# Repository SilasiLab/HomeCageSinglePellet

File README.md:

# **Overview**:

This system allows the user to host up to 5 mice in their home environment and automatically administer the single pellet reaching test to those animals. The system can run unsupervised and continuously for weeks at a time, allowing all 5 mice to perform an unlimited number of single pellet trials at their leisure. 

The design allows a single mouse at a time to enter the reaching tube. Upon entry, the animal’s RFID tag will be read, and if authenticated, a session will start for that animal. A session is defined as everything that happens from the time an animal enters the reaching tube to when they leave the tube. At the start of a session, the animal’s profile will be read and the task difficulty will be automatically adjusted by moving the pellet presentation arm to the appropriate distance away from the reaching tube. After the difficulty is set, pellets will begin being presented with either the left or right presentation arm, depending on which arm is specified in the mouse’s profile. Pellets will continue to be presented periodically until the mouse leaves the tube, at which point the session will end. Video and other data is recorded for the duration of each session. At session end, all the data for the session is saved in an organized way. 

# **Dependencies:**
* Ubuntu v16.04 LTS: Kernel version 4.4.19-35 or later
* Python v3.5.2
	* pySerial	
	* numpy
	* OpenCV v3.4.x
	* tkinter 
	* matplotlib
	* Pillow
	* tqdm
* Flir Spinnaker SDK v1.10.31
	* libavcodec-ffmpeg56
	* libavformat-ffmpeg56
	* libswscale-ffmpeg3
	* libswresample-ffmpeg1
	* libavutil-ffmpeg54
	* libgtkmm-2.4-dev
	* libusb-1.0-0
	
	Note: The Spinnaker dependencies are installed via official Spinnaker SDK install script.
* Arduino IDE v1.8.5

# **Software Installation:**
1. Install Ubuntu 16.04 LTS on your machine.
2. Install Anaconda. (https://www.anaconda.com/distribution/)
3. Install the Flir Spinnaker SDK v1.10.31 **INSERT GOOGLE DRIVE LINK TO SPINNAKER SDK HERE**
4. Install Arduino IDE v1.8.5. (https://www.arduino.cc/en/Main/Software)
5. Install OpenCV for C++.
	- `sudo apt-get install build-essential cmake git libgtk2.0-dev pkg-config libavcodec-dev libavformat-dev libswscale-dev`
	- `sudo apt-get install libjpeg-dev libpng-dev libtiff5-dev libjasper-dev libdc1394-22-dev libeigen3-dev libtheora-dev 			libvorbis-dev libxvidcore-dev libx264-dev sphinx-common libtbb-dev yasm libfaac-dev libopencore-amrnb-dev 			libopencore-amrwb-dev libopenexr-dev libgstreamer-plugins-base1.0-dev libavutil-dev libavfilter-dev 				libavresample-dev`
	- `sudo -s`
	- `cd /opt`
	- Download OpenCV source from https://github.com/opencv/opencv/releases/tag/3.4.4 and unpack it into /opt
	- Download OpenCV_contrib source from https://github.com/opencv/opencv_contrib/releases/3.4.4 and unpack it into /opt
	- `cd opencv`
	- `mkdir release`
	- `cd release`
	- `cmake -D BUILD_TIFF=ON -D WITH_CUDA=OFF -D ENABLE_AVX=OFF -D WITH_OPENGL=OFF -D WITH_OPENCL=OFF -D WITH_IPP=OFF -D 			WITH_TBB=ON -D BUILD_TBB=ON -D WITH_EIGEN=OFF -D WITH_V4L=OFF -D WITH_VTK=OFF -D BUILD_TESTS=OFF -D 				BUILD_PERF_TESTS=OFF -D CMAKE_BUILD_TYPE=RELEASE -D CMAKE_INSTALL_PREFIX=/usr/local -D 						OPENCV_EXTRA_MODULES_PATH=/opt/opencv_contrib/modules /opt/opencv/`
	- `make j4`
	- `make install`
	- `ldconfig`
	- `exit`
	- `cd`
	- `pkg-config --modversion opencv`
	- If everything worked correctly, output should read "3.4.4".
	
5. Create and configure a virtual environment for installing the HomeCageSinglePellet code.
	- `conda create -n <yourenvname> python=3.5.2 anaconda`
	- `conda activate <yourenvname>`
	- `conda install -c conda-forge opencv=3.4.4`
	- `conda install -c anaconda numpy`
	- `conda install -c anaconda pyserial`
	- `conda install -c anaconda tk`
	- `conda install -c conda-forge matplotlib`
	- `conda install tqdm`
	- `conda install Pillow`

6. Download the HCSP source code from https://github.com/SilasiLab/HomeCageSinglePellet and unpack it.
7. Optional (Only if you want to use the analysis features): Install Deeplabcut using the Anaconda based pip installation method. (https://github.com/AlexEMG/DeepLabCut/blob/master/docs/installation.md)
8. Optional (Only if you want to use the anaylsis features): Move the file `HomeCageSinglePellet/src/analysis/HCSP_analyze.py` into `~/.conda/envs/DLC2/lib/python3.6/site-packages/deeplabcut` (Where DLC2 is the name of the anaconda virtual environment where you installed Deeplabcut).
9. Optional (Only if you want to use the anaylsis features): Download our pretrained DLC2 network for automatically extracting reach attempts from your videos. **INSERT GOOGLE DRIVE LINK TO NETWORK HERE**
8. Done!

# **Assembly:**

### **Prerequisites:**

1. Obtain all the parts listed in `HomeCageSinglePellet/resources/partsList.xls`
2. Have the PCB `HomeCageSinglePellet/resources/PCB/nano.brd` manufactured (Find a manufacturer, send them the .brd file using
whatever process they use for upload, wait for it in the mail).
3. 3D print all the .stl files contained in `HomeCageSinglePellet/resources/CAD/STL/`

### **Attach headers and components to the PCB**

1. Attach female headers for the Arduino onto the PCB. Attach male headers onto the CAMTRIG, MSZ, SERVO1, SERVO2, RFID and
IRBREAK holes on the PCB.

2. Solder the stepper driver to the PCB in the orientation shown in the picture. (Note that the holes on 
the PCB are spaced too far apart for the stepper driver pins). To address this we bend the pins of the driver to fit. You'll 
need to do this until someone gets around to fixing the PCB layout.

3. Solder the capacitor across C1 as shown in the picture. (TODO: INSERT PICTURE)

### **Install the voltage regulator and power connectors**

4. Voltage regulator output must be set to 5V by turning the small screw on the blue pot. This is done my powering the device with 12V and recording the output with multimeter while adjusting the pot screw.
Attach 6 leads to the voltage regulator:
	- 2 Leads to the positive input pad.
	- 2 leads to the negative input pad.
	- 1 lead to the positive output pad.
	- 1 lead to the negative output pad.

5. Short the neutral and ground leads on the circular power connectors by soldering a small wire across them.

6. Line up the voltage regulator in the box and drill holes through the box where you want to mount the regulator.

7. Screw one of the circular power connectors into the bottom hole.

8. Solder one of the negative input leads you attached to the voltage regulator in step 1 onto the negative lead of the 
power connector you screwed in in step 4.

9. Solder one of the positive input leads you attached to the voltage regulator in step 1 onto the positive lead of the
power connector you screwed in in step 4. 

10. Place the PCB into the box and drill holes into the box where the mount holes on the PCB line up. 
Then mount the PCB with some bolts. Metal bolts are fine, they won't touch anything that will be a problem. 
Use nylon washers if you're nervous.

11. Solder the remaining positive input power lead that you attached to the voltage regulator in 
step 5 to the positive MOTORPWR pad on the PCB.

12. Solder the remaining negative input power lead that you attached to the voltage regulator in 
step 5 to the negative MOTORPWR pad on the PCB.

13. Screw in the second circular power connector to the remaining hole in the box. Solder a wire from the negative lead of the
second power connector to the negative lead of the first power connctor. Solder a wire from the positive lead of the second power
connector to the positive lead of the first power connector.

### **Assemble the pellet delivery system and mouse tube**

14. Line the hopper rail piece up on the baseplate and screw in the 4 screws that hold it in place.

15. Attach the stepper motor as shown in the picture. Attach the coupler to the shaft of the motor. **Note:** For the steps involving the stepper motor, coupler and coupling screw; We don't yet have a design that uses standard parts. We currently take the screw detailed in the parts list and cut it and the stepper motor shaft to the correct lenght. **INSERT CORRECT LENGTH OF STEPPER MOTOR SHAFT AND COUPLING SCREW HERE.**

16. Attach the screw to the stepper coupler. Slide the hopper onto the rails and insert the nut into the slot where the stepper coupler screw will go. Then thread the shaft coming out of the coupler into the nut. 

17. Rotate the stepper coupler until the screw is all the way into the hopper nut. Solder two leads to the microswitch,
one each on the left and right prongs coming out of the switch. Use superglue to glue the microswitch down so it will be pressed
when the hopper reaches it's closest point to the motor. 

18. Attach both front surface mirrors to the mirror mount piece with double sided tape.

19. Slide the front-wall/mirror holder piece over the end of the acrylic tube.

20. Use your favorite adhesive to attach the IR-Breaker to the IR-Breaker holder.

21. Slide the IR-Breaker holder over the tube so that the beam runs across the bottom of the tube 
(Where the mice feet will be).

22. Hotglue the RFID reader to the acrylic tube as shown.(Note: Push the IR-Breaker holder up against the RFID module so that 
it's sandwiched between the IR-Breaker holder and the front-wall/mirror holder, and hot glue it all in place).

23. Slot the assembled acrylic tube into the square hole on the rail baseplate mount as shown.

24. Line up both servos as shown in the picture. Rotate the servo splines as far as they will go in the 
directions shown in the picture.

25. Use an allen key to insert the set screws into the tips of the hopper arms.

26. Attach the hopper arms to the servo spline as shown in the picture. (Note: This is why we 
rotated the servo spline as far as possible in step 28, so that you can set the maximum retraction 
point of the hopper arms by attaching them how you like).

27. Line the servos with attached hopper arms up as shown in the picture and use your favourite adhesive to 
adhere them to the servo mount points on the hopper. **Note:** This step can be finicky. Before you adhere the servos to the 
hopper, ensure the hopper arms will rotate easily at their pivot point and that they slide easily through the holes in the 
hopper. If there is too much friction the arms will vibrate and jump around as they move, and since their function is to 
balance millet seeds on a small set screw, vibrations are bad.

28. This step is where we will glue the acrylic tube permanently into the sqaure 3D printed hole it sits in. Rotate the stepper
coupler until the hopper is as close as it can get to the motor. Now rotate the hopper arms up so that they are sitting infront 
of the tube opening as shown. On bootup the stepper motor will "zero" the hopper using the limit switch. We want this zero point
to put our pellet presentation arms directly infront of the tube opening. Additionally we want the tube to sit at a high enough angle that the hopper will not catch on the mirrors or any part of the tube assembly when it moves. Once you're satisfied that both these requirements are met, glue the tube into place. 

29. Splice the power wires of both servo motors together. Splice the ground wires of both servo motors together. Splice the servo power wire into the lead coming out of the voltage regulator positive output. Splice the servo ground wire into the lead coming out of the voltage regulator negative output.

30. Plug the leftmost servo signal wire into the SERV02 signal pin on the PCB. Plug the rightmost servo signal wire into the 
SERVO1 signal pin on the PCB.

31. Splice the power wires of the IRbreak LED and photo diode together. Splice the ground wires of the IRBreak LED and photo diode together. Plug the spliced power, spliced ground and signal line of the IRbreaker into the IRBREAK pins on the PCB. 

32. Plug the microswitch wires into the MSZ pins on the PCB. (TODO: Figure out which wire goes onto which pin and add a picture)

33. Plug the 12V 1A power supply into either of the circulaer power connectors on the PCB box.

34. Plug one of the micro USB cables into the Arduino on one end and the PC on the other.

35. Plug one of the micro USB cables into the Arduino on one end and the PC on the other.

36. Assembly complete!
 
# **Calibration and Configuration:**

1. You'll need to upload the `HomeCageSinglePellet/src/arduino/homecage_server/homecage_server.ino` file to the Arduino. 
(https://www.arduino.cc/en/Guide/ArduinoNano)
NB.:
* A. After a fresh install of Ubuntu, there may be issues accessing serial ports. Run the following command to give full access: sudo usermod -a -G dialout $USER  (in our case user: silasi).
* B. Use following setting in Arduino IDE: 
	- 1. Tools -> Board -> Arduino Nano
	- 2. Tools -> Processor -> Atmega 328P (Old Bootloader)
2. There are 4 constants that will need to be modified in the file
`HomeCageSinglePellet/src/arduino/homecage_server/homecage_server.ino`
They are: `SERVO1_UP_POS`, `SERVO1_DOWN_POS`, `SERVO2_UP_POS` and `SERVO2_DOWN_POS`. They are located
on lines 41,43,45 and 47 respectively. These constants represent the PWM signal going to each servo. I won't explain PWM here,
all you need to know is different numbers correspond to different positions for the servos. In the main loop, lines 421-425 
have a block that will make the arms go up and down one at a time in an infinite loop. You'll need to observe the up/down 
positions of the arms during these movements to dial in the correct position, using the constants mentioned above. I haven't 
found a better way to do this yet, and frankly all the arduino code is poorly written. Any improvements or a rewrite would be 
welcomed. Once you're happy with the up/down position of each arm during their "pellet presenting" movements, comment 
the infinite loop out and upload to the Arduino.
	
2. Open `HomeCageSinglePellet/config/config.txt` and set the path to your `HomeCageSinglePellet/AnimalProfiles/` 
directory. (One of the Spinnaker video writing functions doesn't work with relative paths so we chose to work with 
full paths). I believe python has a library that will turn a relative path into a full path, so this could be fixed in 
the future.
	
3. We don't provide exact details on camera setup, but if you want to use the analysis features provided in this 
project, it will be important to have video recording conditions as close as possible to ours. The performance of 
deelabcut will degrade rapidly as conditions stray from those used to produce the frames used to train the network.
Additionally the functions in kinalyze.py are dependent on specific recording conditions. If you plan to use the analysis 
features, leave the recording settings in `HomeCageSinglePellet/config/config.txt` as the default. In terms of lighting 
conditions, camera mounting, recording angle, etc, just do your best to make it look like the picture below. If it's close 
enough, the analysis pipeline will work. **INSERT PICTURE OF FRAME CAPTURED BY PTGREY**

# **Usage**:
### **Running the Device**
1. Enter the virtual environment that the system was installed in by typing `source activate <my_env>` into a terminal.

2. Use `cd` to navigate to HomeCageSinglePellet/src/client/ and then run `python -B genProfiles.py`. The text prompts will walk you through entering your new animals into the system.

3. Open HomeCageSinglePellet/config/config.txt and set the system configuration you want.

4. Enter HomeCageSinglePellet/src/client/ and run `python -B main.py`

5. To test that everything is running correctly, block the IR beam breaker with something
	and scan one of the system’s test tags. If a session starts properly, it’s working.

6. To shut the system down cleanly; 

	- Ensure no sessions are currently running. 
	- Press the quit button on the GUI.
	- Ctrl+c out of the program running in the terminal.
NB.
1. Arduino needs to be USB0 , and RFID reader needs to be USB1. You can see connected USB devices with terminal command:
ls /dev/tty*

### **Analysis**:

A high level analysis script is provided that runs the data for all animals through a long analysis pipeline. The functions performed on each video include;

* Analyze with Deeplabcut2.
* Identify all reaching attempts and record frame indexes where reaches occur.
* Compute 3D trajectory of reaches and estimate magnitude of movement in millimeters.
* Cut videos to remove any footage not within the bounds of a reaching event.
* Neatly package data for each analyzed video in a descriptively named folder within the animals ./Analyses/ directory.

This analysis is started by entering the HomeCageSinglePellet/src/analysis/ directory and running
`bash analyze_videos.sh <CONFIG_PATH> <VIDEO_DIRECTORY> <NETWORK_NAME>`

This script takes the following input;

**CONFIG_PATH** = Full path to config.yaml file in root directory of DLC2 project.

**VIDEO_DIRECTORY** = Full path to directory containing videos you want to analyze. (e.g <~/HomeCageSinglePellet/AnimalProfiles/MOUSE1/Videos/>)

**NETWORK_NAME** = Full name of DLC2 network you want to use to analyze videos. (e.g <DeepCut_res
net50_HomeCageSinglePelletNov18shuffle1_950000>)

Another script (`HomeCageSinglePellet/src/analysis/scoreTrials.py`) is provided for manually categorizing reaches once they have been identified in the step detailed above. This script opens a GUI that allows the user to select an animal and browse through all the videos that have been analyzed for that animal. (In the video list, blue videos indicate videos where reaches were detected by the analysis software. Beige videos indicate videos where no reaches were detected. Green videos indicate videos that have already been manually scored). When users select a video from the list, the video window will display the first detected reach in a loop. It will also display the "reach count" (e.g 1/16) to indicate how many reaches the video contains and which one is currently being viewed. The user can then use the mouse or a hotkey to place the current reach into a category. The video window will then jump to the next reach. This repeats until all the reaches for a given video are scored, at which point the category information will be saved. 

**Note:** All the analysis functions read and write all their data to/from `HomeCageSinglePellet/AnimalProfiles/<animal_name>/Analyses/`. Information for each video is saved in a unique folder whose name includes video creation date, animal RFID, cage number and session number. (e.g `2019-01-25_14:36:31_002FBE737B99_67465_5233`). Each of these folders will contain the raw video, the deeplabcut output from analyzing the video (.h5 and .csv formats). In addition, if >=1 reaches were found in the video, the folder will contain a file named date_time_rfid_cage_number_session_number_reaches.txt (e.g `2019-01-25_14:36:31_002FBE737B99_67465_5233_reaches.txt`). This file contains the start and stop frame indexes of each reach in the video and (x,y,z) vectors for each reach. In addition, once a video has been scored manually using `scoreTrials.py`, a file named date_time_rfid_cage_number_session_number_reaches_scored.txt (e.g `2019-01-25_14:36:31_002FBE737B99_67465_5233_reaches_scored.txt`) will be added to the video's folder. This file is the same as date_time_rfid_cage_number_session_number_reaches.txt, except that it also contains a category identifier for every reach.

# **Troubleshooting**:

* Is everything plugged in?
* Shutting the system down incorrectly will often cause the camera and camera software to enter a bad state.
	* Check if the light on the camera is solid green. If it is, unplug the camera and plug it back in.
	* Check the HomeCageSinglePellet/src/client/ directory for a file named KILL. If this file exists, delete it.
	* Make sure the camera is plugged into a USB 3.0 or greater port and that it is not sharing a USB bridge with too many 			other devices (I.e if you have 43 devices plugged into the back of the computer and none in the front, plug the 		camera into the front).
* Make sure you are in the correct virtual environment.
* Make sure the HomeCageSinglePellet/config/config.txt file contains the correct configuration. (If the file gets deleted it will be replaced by a default version at system start)
* Make sure there are 1 to 5 profiles in the HomeCageSinglePellet/AnimalProfiles/ directory. Ensure these profiles contain all 		the appropriate files and that the save.txt file for each animal contains the correct information. 
* Make sure that the Arduino mounted as device ttyUSB0 and that the RFID reader mounted as ttyUSB1 in /dev/. If they mounted 
differently, rebooting and attaching them in the correct order will fix the problem.

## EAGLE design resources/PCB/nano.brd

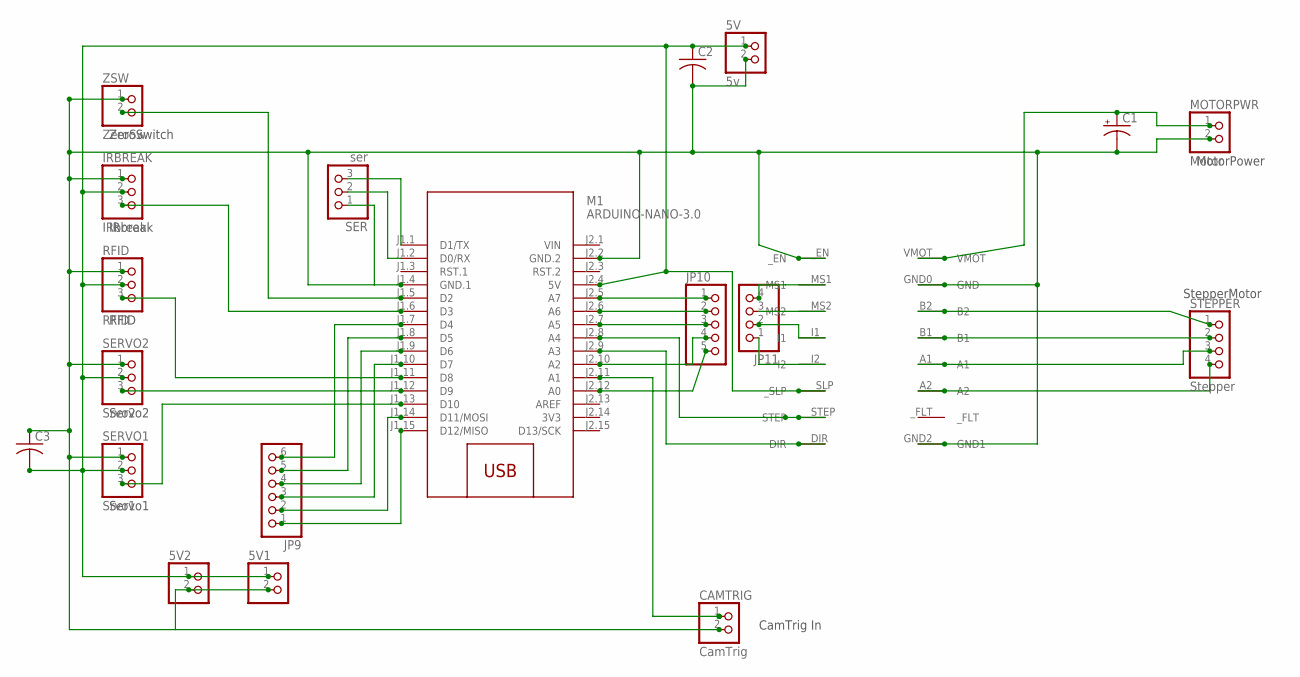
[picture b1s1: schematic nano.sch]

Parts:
5V: 5v; 1X02
5V1, 5V2: PINHD-1X2; 1X02
C1: CPOL-USE5-5; E5-5
C2, C3: C-USC0805; C0805
CAMTRIG: CamTrig; 1X02
IRBREAK: IRbreak; 1X03
JP9: PINHD-1X6; 1X06
JP10: PINHD-1X5; 1X05
JP11: PINHD-1X4; 1X04
M1: ARDUINO-NANO-3.0
MOTORPWR: Motor; 1X02
RFID: RFID; 1X03
SER: ser; 1X03
SERVO1: Srvo1; 1X03
SERVO2: Srvo2; 1X03
STEPPER: Stepper; 1X04
U$1: MP6500
ZSW: ZeroSw; 1X02

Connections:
3V3: M1.J2.14 (3V3)
unnamed: C1.+, MOTORPWR.1, U$1.VMOT
unnamed: JP9.1, M1.J1.15 (D12/MISO)
unnamed: JP11.4, U$1.MS1
unnamed: STEPPER.4, U$1.A2
unnamed: STEPPER.3, U$1.A1
unnamed: STEPPER.2, U$1.B1
unnamed: STEPPER.1, U$1.B2
unnamed: JP9.2, M1.J1.14 (D11/MOSI)
unnamed: JP9.3, M1.J1.10 (D7)
unnamed: M1.J1.12 (D9), SERVO2.3
unnamed: M1.J1.13 (D10), SERVO1.3
unnamed: M1.J1.5 (D2), ZSW.2
unnamed: IRBREAK.3, M1.J1.6 (D3)
unnamed: M1.J1.11 (D8), RFID.3
unnamed: CAMTRIG.1, M1.J2.11 (A1)
unnamed: M1.J2.9 (A3), U$1.DIR
unnamed: M1.J2.8 (A4), U$1.STEP
unnamed: JP9.4, M1.J1.9 (D6)
unnamed: 5V.1, 5V1.1, 5V2.1, C2.1, C3.2, IRBREAK.2, M1.J2.4 (5V), RFID.2, SERVO1.2, SERVO2.2, U$1._SLP
unnamed: JP9.5, M1.J1.8 (D5)
unnamed: JP9.6, M1.J1.7 (D4)
unnamed: JP10.1, M1.J2.5 (A7)
unnamed: JP10.2, M1.J2.6 (A6)
unnamed: JP10.3, M1.J2.7 (A5)
unnamed: JP10.4, M1.J2.10 (A2)
unnamed: JP10.5, M1.J2.12 (A0)
unnamed: 5V.2, 5V1.2, 5V2.2, C1.-, C2.2, C3.1, CAMTRIG.2, IRBREAK.1, M1.J1.4 (GND.1), M1.J2.2 (GND.2), MOTORPWR.2, RFID.1, SER.1, SERVO1.1, SERVO2.1, U$1.GND0 (GND), U$1.GND2 (GND1), U$1._EN, ZSW.1
unnamed: JP11.3, U$1.MS2
unnamed: JP11.2, U$1.I1
unnamed: JP11.1, U$1.I2
unnamed: M1.J1.1 (D1/TX), SER.3
unnamed: M1.J1.2 (D0/RX), SER.2
VIN: M1.J2.1 (VIN)

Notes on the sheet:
Servo1
Servo2
RFID
IRbreak
ZeroSwitch
StepperMotor
MotorPower
CamTrig In

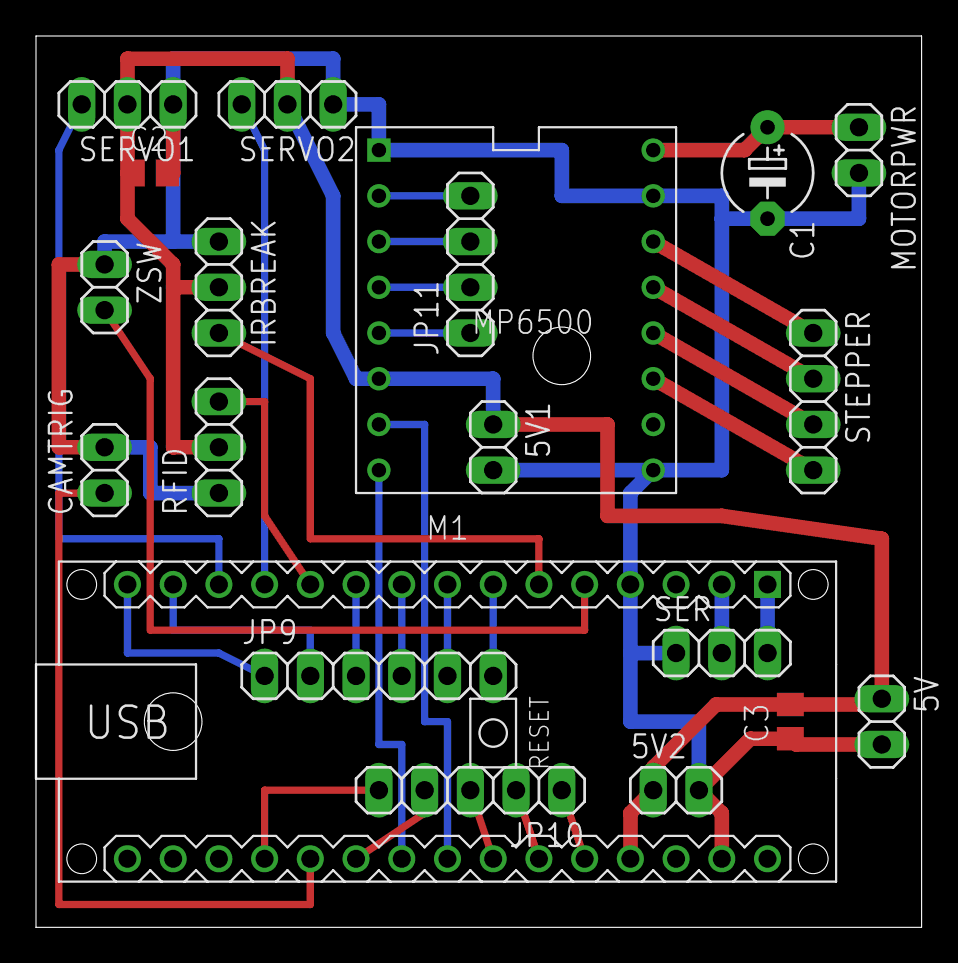
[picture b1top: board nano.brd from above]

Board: 2 copper layers, 49.2 x 49.5 mm, 20 parts (0 on the bottom side), 32 nets.

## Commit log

2018-01-05 Implemented RFID proximity detection and fixed tty buffer issues
2018-01-08 Merged RFID Proximity and IR into GPIO_Control.py and refactored servo control code
2018-01-08 Fixed several typos
2018-01-10 Added camera live feed
2018-01-11 Refactored a bit and started implementing AnimalProfile class
2018-01-11 Started implementing SessionController
2018-01-12 Started putting camera,RFID and servo control into their own classes.
2018-01-12 Version 1 completed. Needs lots of refactoring.
2018-01-13 Refactored
2018-01-13 Renamed SPAutomation.py to main.py
2018-01-15 String formatting, function simplification
2018-01-22 Implemented IR pressence detection, camera recording in separate process and refactored a bit.
2018-01-22 Fixed many typos
2018-01-23 Implemented video recording in forked process and modified existing functions to take advantage of this.
2018-01-23 Made it so PWM signal shuts down after servo moves
2018-01-23 Fixed bugs in camera sub process and implemented PWM kill switch
2018-01-23 Fixed RFID so it is parsed correctly
2018-01-24 Moved servo-arm-cycle to it's own process and improved SessionController.startSession() accordingly
2018-01-24 Fixed bug where RFID tag could be read during an in-progress session, filling the serial buffer.
2018-01-25 Implemented basic logging capability
2018-01-25 Added debug logging to servo process and entered correct RFID profiles for live test
2018-01-30 Worked on commenting things better
2018-02-07 Implemented pellet detection feature
2018-02-07 Debugged and fixed typos
2018-02-07 Put trial_count into session_history logs so we can track trial numbers
2018-03-01 A bunch of minor, random changes...
2018-03-01 Formatted source files to work with Geany
2018-03-01 Added stepper motor control for XY bed feature
2018-03-02 Improved XY bed feature and moved stepper control to long-lived process
2018-03-02 Cleaned things up before weekend overnight test
2018-03-02 Final touchups before weekend overnight test
2018-03-05 Started adding profile save/load feature
2018-03-05 Finished AnimalProfile save/load feature
2018-03-09 Added basic graphing capability of AnimalProfile logs
2018-03-09 Improved comments on some files
2018-03-12 Modified comments
2018-03-12 Finished commenting and moved video path generation to AnimalProfile instead of SessionController.
2018-03-13 Improved console output messages
2018-03-13 Configuring for live use
2018-03-14 Increased stepper motor speed
2018-03-16 Added script to process session_history.csv files into format with human readable date and time for working in excel
2018-04-11 Implementing some of feature backlog from April_10. (untested)
2018-04-12 XY bed now stops immediately when session ends, mouse difficulty level is specified in mm, and log file now has human readable dates instead of timestamps
2018-04-13 Began testing GUI
2018-04-13 Changed AnimalProfile save file format to include more information
2018-04-13 Finished first version of config GUI
2018-06-06 Updating git repo with PC/Arduino/Ptgrey port
2018-06-06 Made it possible to build ptgrey binary from project directory
2018-06-06 Made a dependency list in the INSTALL.txt file
2018-06-11 synced up servo movement signals after Ralph fixed servo wiring
2018-06-20 Updated magic numbers...
2018-07-10 Fixed camera de-initialization failure race condition
2018-07-14 Fixed GUI so animal profile changes made by users will be seen at runtime (untested)
2018-07-16 Removed log file
2018-07-16 Implemented preview window for Spinnaker camera
2018-07-16 Removing camera.py because PS3 camera no longer being used
2018-07-20 Ported plotting function from RPi version to new Arduino/PC version
2018-07-27 Initial commit of DeepLabCut output processing pipeline
2018-07-29 Implemented "Event Extraction" logic for pose event extraction
2018-08-02 Changed Pandas dataframe access from .values to .iat for 100x script speedup
2018-08-13 Implemented analysis scripts for finding successful reaches in video
2018-08-15 Modified config in preparation of running v1.0
2018-08-17 Modified calibration constants....need to put config in environ vars
2018-08-21 Untested fix for AVIOpen hang issue caused by bad string arg
2018-08-24 Set theme jekyll-theme-slate
2018-09-03 Started Successful Reach vs Time graph implementation
2018-09-03 Cleaning up
2018-09-19 Implemented shutdown button in GUI
2018-09-19 Hotfix for GUI
2018-09-19 Made pellet presentation max distance 5 because any higher will derail the hopper
2018-10-22 Added configuration file for spinnaker process.
2018-10-25 Added kinematic analysis to analysis directory
2018-10-25 Did a lot of stuff for fully-automated kinematic 3D-reconsutrction pipeline
2018-10-25 Refactored a tiny bit
2018-10-31 Finished kinalyze dlc point filtering and event parsing
2018-11-04 Finished kinalyze.py
2018-11-21 Swapped out servo library for official Arduino one. Solves servo shooting up problem but introduces servo at-rest jitter
2018-11-21 Removed contents of AnimalProfiles directory....should not have data on github
2018-11-21 Adding AnimalProfiles directory back in....we want the directory here...just needs to be empty
2018-11-21 Changed video file name format, refactored a bit
2018-11-21 TEST tags now bypass config and default to 50FPS and DisplayPreview=True
2018-11-29 Kinalyze is now usable for extracting reaches from videos and generating 3D trajectory reconstructions of those reaches
2018-11-30 Implemented bash wrapper for analyzing directories of videos with DLC and trajectory reconstruction
2018-12-04 Removed deprecated files
2018-12-11 Started implementing semi-auto trial scoring GUI
2018-12-11 Moved RFID functionality to python client
2018-12-12 Made servos detach after every movement (This no longer stalls with Servo.h since removing softwareserial calls). End result is no more jittering!
2019-01-15 ghetto merge
2019-01-15 Updated scoring GUI to prevent videos being cut off as early
2019-01-17 Implemented buttons to select which presenting arm to use for each animal (untested)
2019-01-17 Tested pellet presenting arm control buttons for main gui
2019-01-17 Refactored resources directory structure and added updated ptgrey camera post mount
2019-01-17 Inreased size of through holes on ptgrey camera mount
2019-01-18 Implemented unused video deletion script
2019-01-21 Change kinematic analysis to pad end of events with configurable number of frames
2019-01-21 add pellet classifier
2019-01-22 add the weights of the pellet classification model
2019-01-28 A bunch of changes
2019-01-30 Started documenting system componentsY
2019-01-31 Continuing to comment + document
2019-01-31 Continuing to comment and document
2019-02-01 Last of comments targeted at future maintainers
2019-02-01 First iteration of user documentation
2019-02-01 Rename README.txt to README.md
2019-02-05 Adding first help image
2019-02-05 Implemented profile generator function and a directory structure integrity check function
2019-02-06 Added Deeplabcut cli interface file for bash analysis script
2019-02-06 delete
2019-02-06 signing everything and adding contact info
2019-02-06 Adding PCB enclosure CAD files
2019-02-07 Adding frank's analysis summary feature to scoringGUI save process
2019-02-08 Removed padding in scoring GUI reach videos since it's already being added at the source by kinalyze.py setting the frame indexes with padding
2019-02-14 fix the bug that analysis script crush when the reach in output of deeplabcut is empty.
2019-02-14 Updating hardcoded file path to reflect new project structure
2019-02-19 Change the comments for functions in analysis.py
2019-02-25 Uploading assembly pictures
2019-02-25 Scaling all the assembly pictures to reduce size
2019-02-26 More assembly pictures
2019-02-27 Implemented daily trial limit feature. User can use GUI to set animal trial limit per day. Rests at 7am.
2019-02-27 Bug fixes for session limit feature
2019-02-28 Uploading more pictures for docs
2019-03-01 Modified the formate of analysed csv file.
2019-03-01 Fix the calculatiion for reaching frame
2019-03-11 modified the readme.md
2019-03-25 add the model and the tool to retrain deeplabcut and predict on new videos with it.
2019-03-26 Fixed bugs.

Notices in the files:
parts and their libraries:
diy-modules: Released under the Creative Commons Attribution 4.0 International License: http://creativecommons.org/licenses/by/4.0
